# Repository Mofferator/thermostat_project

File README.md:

# IoT Temperature Sensor Project
My thermostat is a compulsive liar, and I started this project to prove it!

## Hardware
- The hardware for this project consists of an ESP32 which reads the temperature and humidity from a HDC1080 air sensor
- The board also features a usb to uart (cp2102) converter, enabling easy uploading of code in the development process

## Firmware
- The basic operation of the device is as follows
  - Read the temperature and humidity
  - Connect to the specified wifi network if possible
  - Serialize the environment data into json and send to webserver via HTTP request
  - disconnect from wifi
  - Enter deep sleep for a configurable number of seconds

## Server
- The webserver containerized, consisting of a python flask web server and a MySQL database.
- The webserver also has several webpages where the temperature readings from the various devices and rooms can be viewed

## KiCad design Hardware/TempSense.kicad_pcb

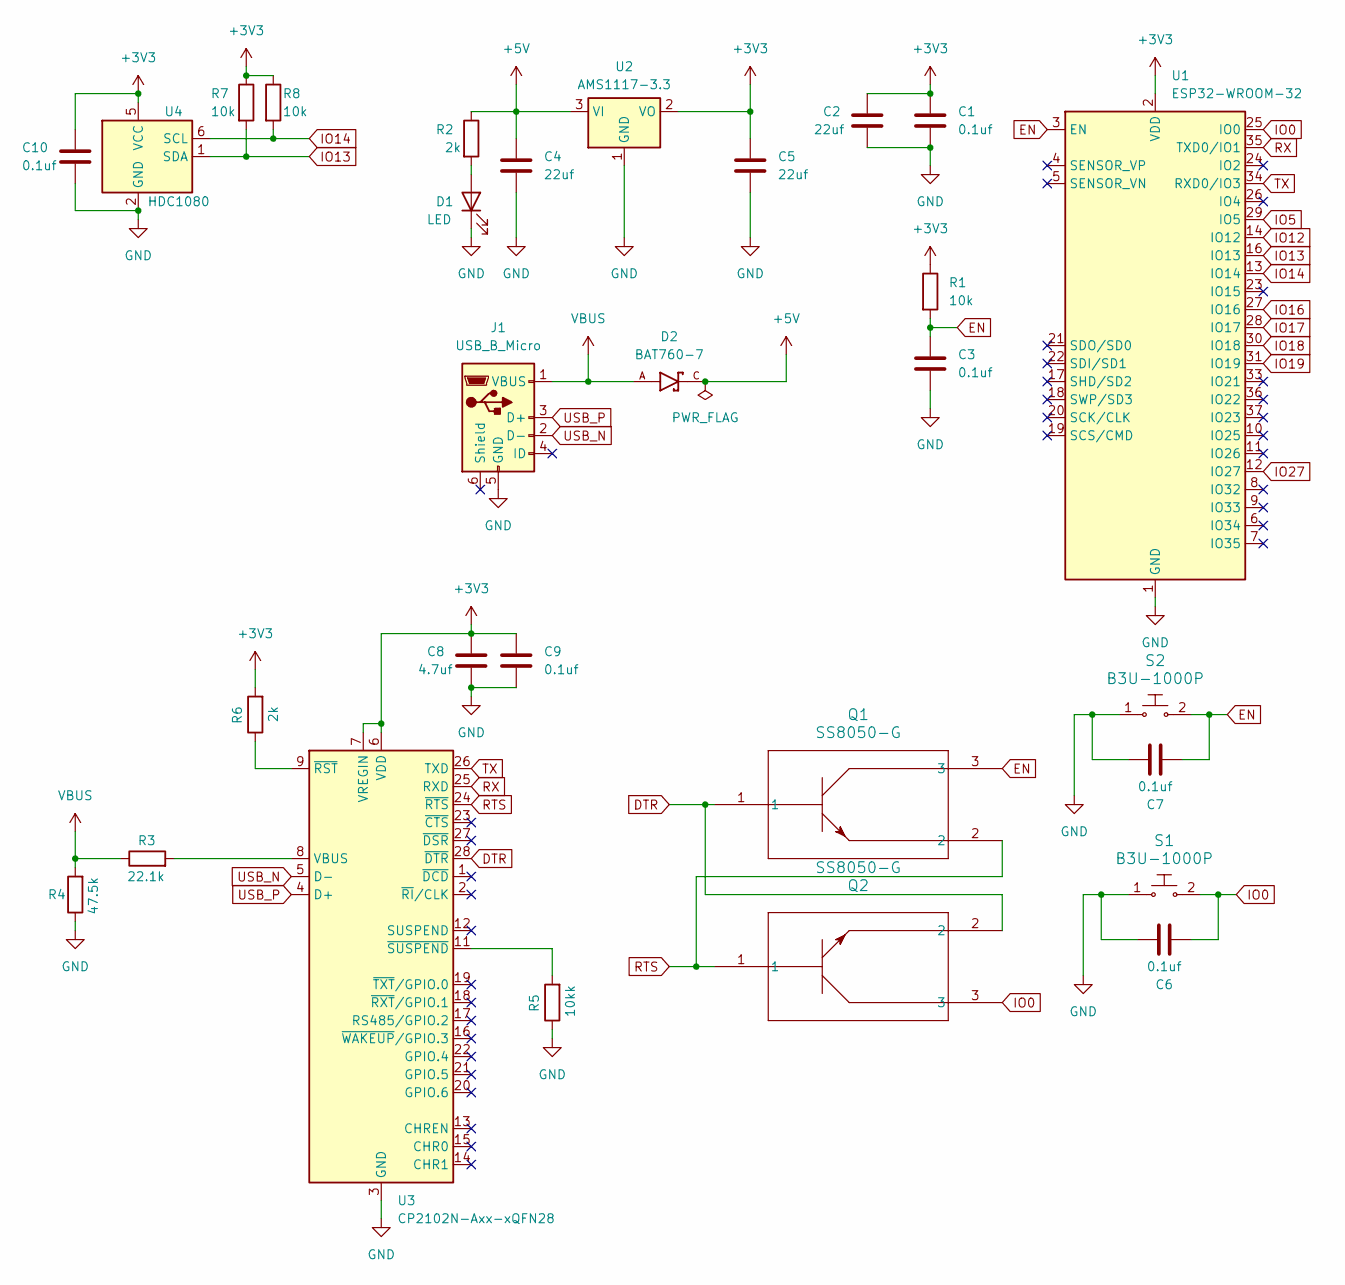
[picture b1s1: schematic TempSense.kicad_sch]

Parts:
C1, C3, C6, C7, C9, C10: 0.1uf; C_0402_1005Metric
C2, C4, C5: 22uf; C_0603_1608Metric
C8: 4.7uf; C_0402_1005Metric
D1: LED; LED_0603_1608Metric
D2: BAT760-7; SOD2513X120N; PARTREV 9-2
J1: USB_B_Micro; USB_Micro-B_Molex_47346-0001
Q1, Q2: SS8050-G; TRAN_SS8050-G_CIP
R1, R7, R8: 10k; R_0402_1005Metric
R2, R6: 2k; R_0402_1005Metric
R3: 22.1k; R_0402_1005Metric
R4: 47.5k; R_0402_1005Metric
R5: 10kk; R_0402_1005Metric
S1, S2: B3U-1000P; SW_Push_1P1T_XKB_TS-1187A; MPN B3U-1000P; Digi-Key_PN SW1020CT-ND
U1: ESP32-WROOM-32
U2: AMS1117-3.3; SOT-223-3_TabPin2
U3: CP2102N-Axx-xQFN28; QFN-28-1EP_5x5mm_P0.5mm_EP3.35x3.35mm
U4: HDC1080; Texas_PWSON-N6

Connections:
+3V3: C1.1, C2.1, C5.1, C8.1, C9.1, C10.1, R1.1, R6.2, R7.1, R8.1, U1.2 (VDD), U2.2 (VO), U3.6 (VDD), U3.7 (VREGIN), U4.5 (VCC)
+5V: C4.1, D2.C, R2.1, U2.3 (VI)
DTR: Q1.1, Q2.2, U3.28 (~DTR)
EN: C3.1, C7.2, Q1.3, R1.2, S2.2, U1.3 (EN)
GND: C1.2, C2.2, C3.2, C4.2, C5.2, C6.1, C7.1, C8.2, C9.2, C10.2, D1.1 (K), J1.5 (GND), R4.1, R5.1, S1.1, S2.1, U1.1 (GND), U1.15 (GND), U1.38 (GND), U1.39 (GND), U2.1 (GND), U3.3 (GND), U3.29 (GND), U4.2 (GND)
IO0: C6.2, Q2.3, S1.2, U1.25 (IO0)
IO5: U1.29 (IO5)
IO12: U1.14 (IO12)
IO13: R7.2, U1.16 (IO13), U4.1 (SDA)
IO14: R8.2, U1.13 (IO14), U4.6 (SCL)
IO16: U1.27 (IO16)
IO17: U1.28 (IO17)
IO18: U1.30 (IO18)
IO19: U1.31 (IO19)
IO27: U1.12 (IO27)
unnamed: D1.2 (A), R2.2
unnamed: R3.2, U3.8 (VBUS)
unnamed: R6.1, U3.9 (~RST)
unnamed: R5.2, U3.11 (~SUSPEND)
RTS: Q1.2, Q2.1, U3.24 (~RTS)
RX: U1.35 (TXD0/IO1), U3.25 (RXD)
TX: U1.34 (RXD0/IO3), U3.26 (TXD)
USB_N: J1.2 (D-), U3.5 (D-)
USB_P: J1.3 (D+), U3.4 (D+)
VBUS: D2.A, J1.1 (VBUS), R3.1, R4.2

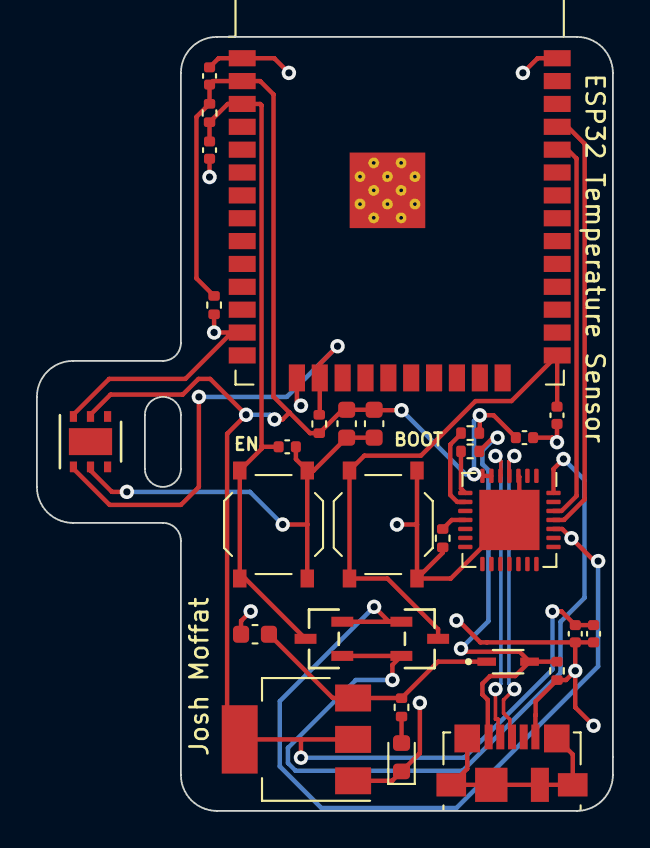
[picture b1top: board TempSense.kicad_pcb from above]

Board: 2 copper layers, 32.0 x 43.0 mm, 29 parts (0 on the bottom side), 18 nets.

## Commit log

2023-05-03 Added docker configuration to a hello world state
2023-05-03 Added DDL for basic database to hold temperature data and device info
2023-05-03 Added sample data to initdb.sql as well as a basic route showing it
2023-05-03 Added POST route to handle adding of data to database
2023-05-05 Added healthchecks to docker compose to ensure DB is running
2023-05-05 Added arduino PlatformIO project
2023-05-05 Configured send_data func to read current time and temperature
2023-05-12 Added web gui
2023-05-12 Added templates
2023-05-13 Fleshed our /room/ routes
2023-12-18 Edited setup for sql
2023-12-18 Removed extraneous files
2023-12-18 Moved json.hpp to include folder
2023-12-18 Abstracted main loop into servermanager class and added deep sleep between readings
2023-12-18 Changed interval to 60s
2023-12-19 Renamed folder for firmware
2023-12-19 Moved server side files into server folder
2023-12-19 Added kicad files from hardware
2023-12-19 Added labels to shematic and produced pdf version
